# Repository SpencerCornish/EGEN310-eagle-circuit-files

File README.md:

# EGEN310-eagle-circuit-files

A schematic and board layout for the EGEN310 Cat's Conundrum car project

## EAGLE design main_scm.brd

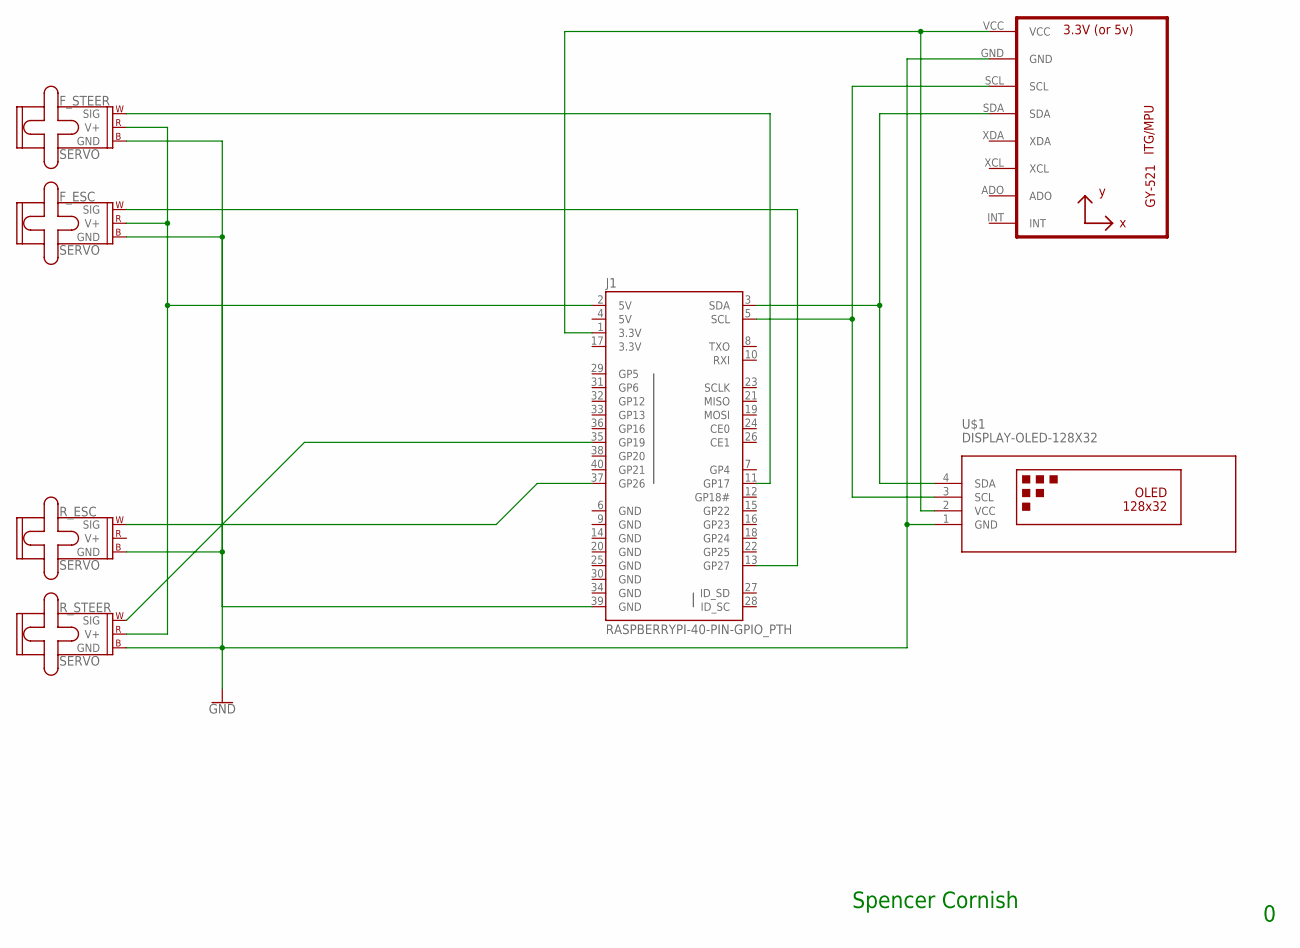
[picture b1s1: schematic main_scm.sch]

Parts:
F_ESC: SERVO; 1X03
F_STEER: SERVO; 1X03
J1: RASPBERRYPI-40-PIN-GPIO_PTH; 2X20_SHROUDED
R_ESC: SERVO; 1X03
R_STEER: SERVO; 1X03
U1: GY-521MPU6050; GY-521
U$1: DISPLAY-OLED-128X32

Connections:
3.3V: J1.17 (3.3V)
5V: J1.4 (5V)
GND: F_ESC.3 (GND), F_STEER.3 (GND), J1.6 (GND), J1.9 (GND), J1.14 (GND), J1.20 (GND), J1.25 (GND), J1.30 (GND), J1.34 (GND), J1.39 (GND), R_ESC.3 (GND), R_STEER.3 (GND), U1.GND, U$1.1 (GND)
unnamed: J1.1 (3.3V), U1.VCC, U$1.2 (VCC)
unnamed: F_ESC.2 (V+), F_STEER.2 (V+), J1.2 (5V), R_STEER.2 (V+)
unnamed: J1.3 (SDA), U1.SDA, U$1.4 (SDA)
unnamed: J1.5 (SCL), U1.SCL, U$1.3 (SCL)
unnamed: J1.35 (GP19), R_STEER.1 (SIG)
unnamed: F_ESC.1 (SIG), J1.13 (GP27)
unnamed: J1.37 (GP26), R_ESC.1 (SIG)
unnamed: F_STEER.1 (SIG), J1.11 (GP17)

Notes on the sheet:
Spencer Cornish

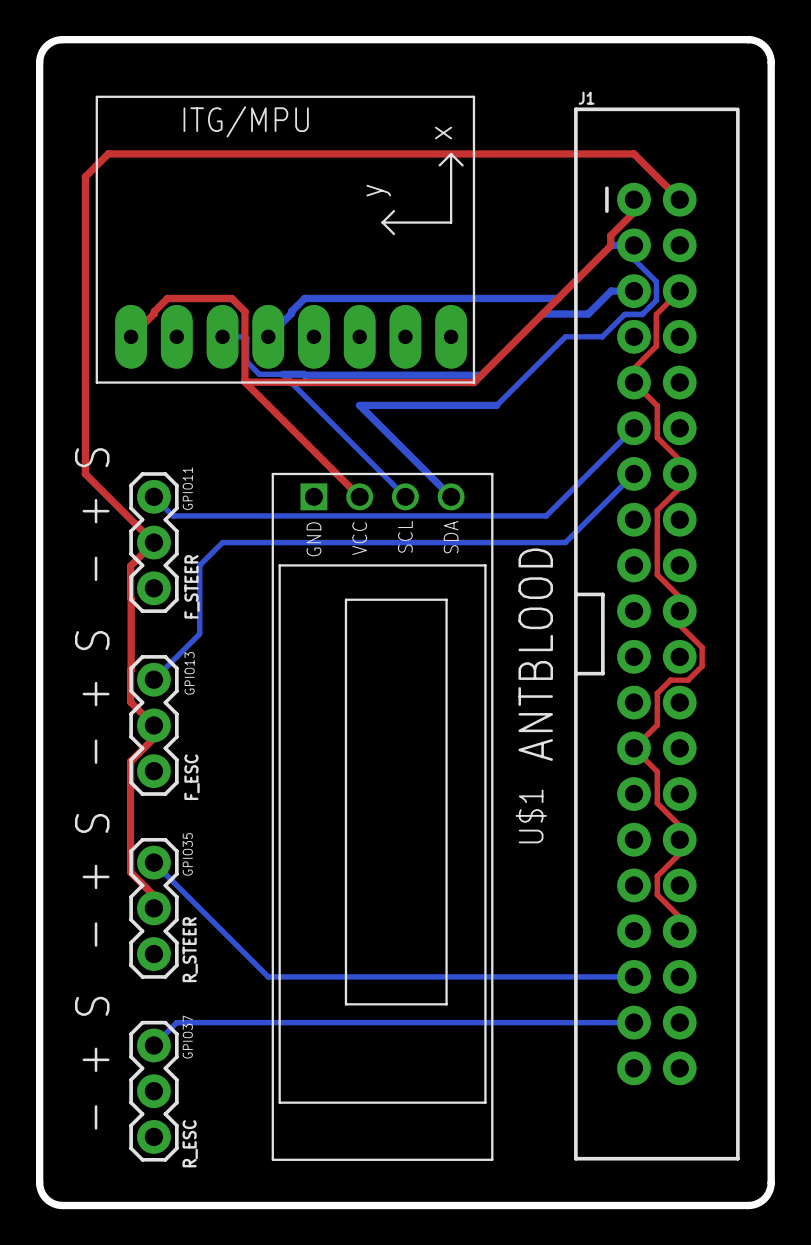
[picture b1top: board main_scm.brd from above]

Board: 2 copper layers, 40.6 x 64.8 mm, 7 parts (0 on the bottom side), 9 nets.

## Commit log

2018-12-07 Add CAM files

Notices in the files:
parts and their libraries:
SparkFun-Electromechanical: Licensing: Creative Commons ShareAlike 4.0 International - https://creativecommons.org/licenses/by-sa/4.0
diy-modules: Released under the Creative Commons Attribution 4.0 International License: http://creativecommons.org/licenses/by/4.0
